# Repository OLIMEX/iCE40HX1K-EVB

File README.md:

# iCE40HX1K-EVB
FPGA development board made with KiCAD

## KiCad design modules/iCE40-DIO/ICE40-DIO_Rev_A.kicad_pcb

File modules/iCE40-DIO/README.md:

# Repository re-located here: https://github.com/OLIMEX/iCE40-DIO/tree/master

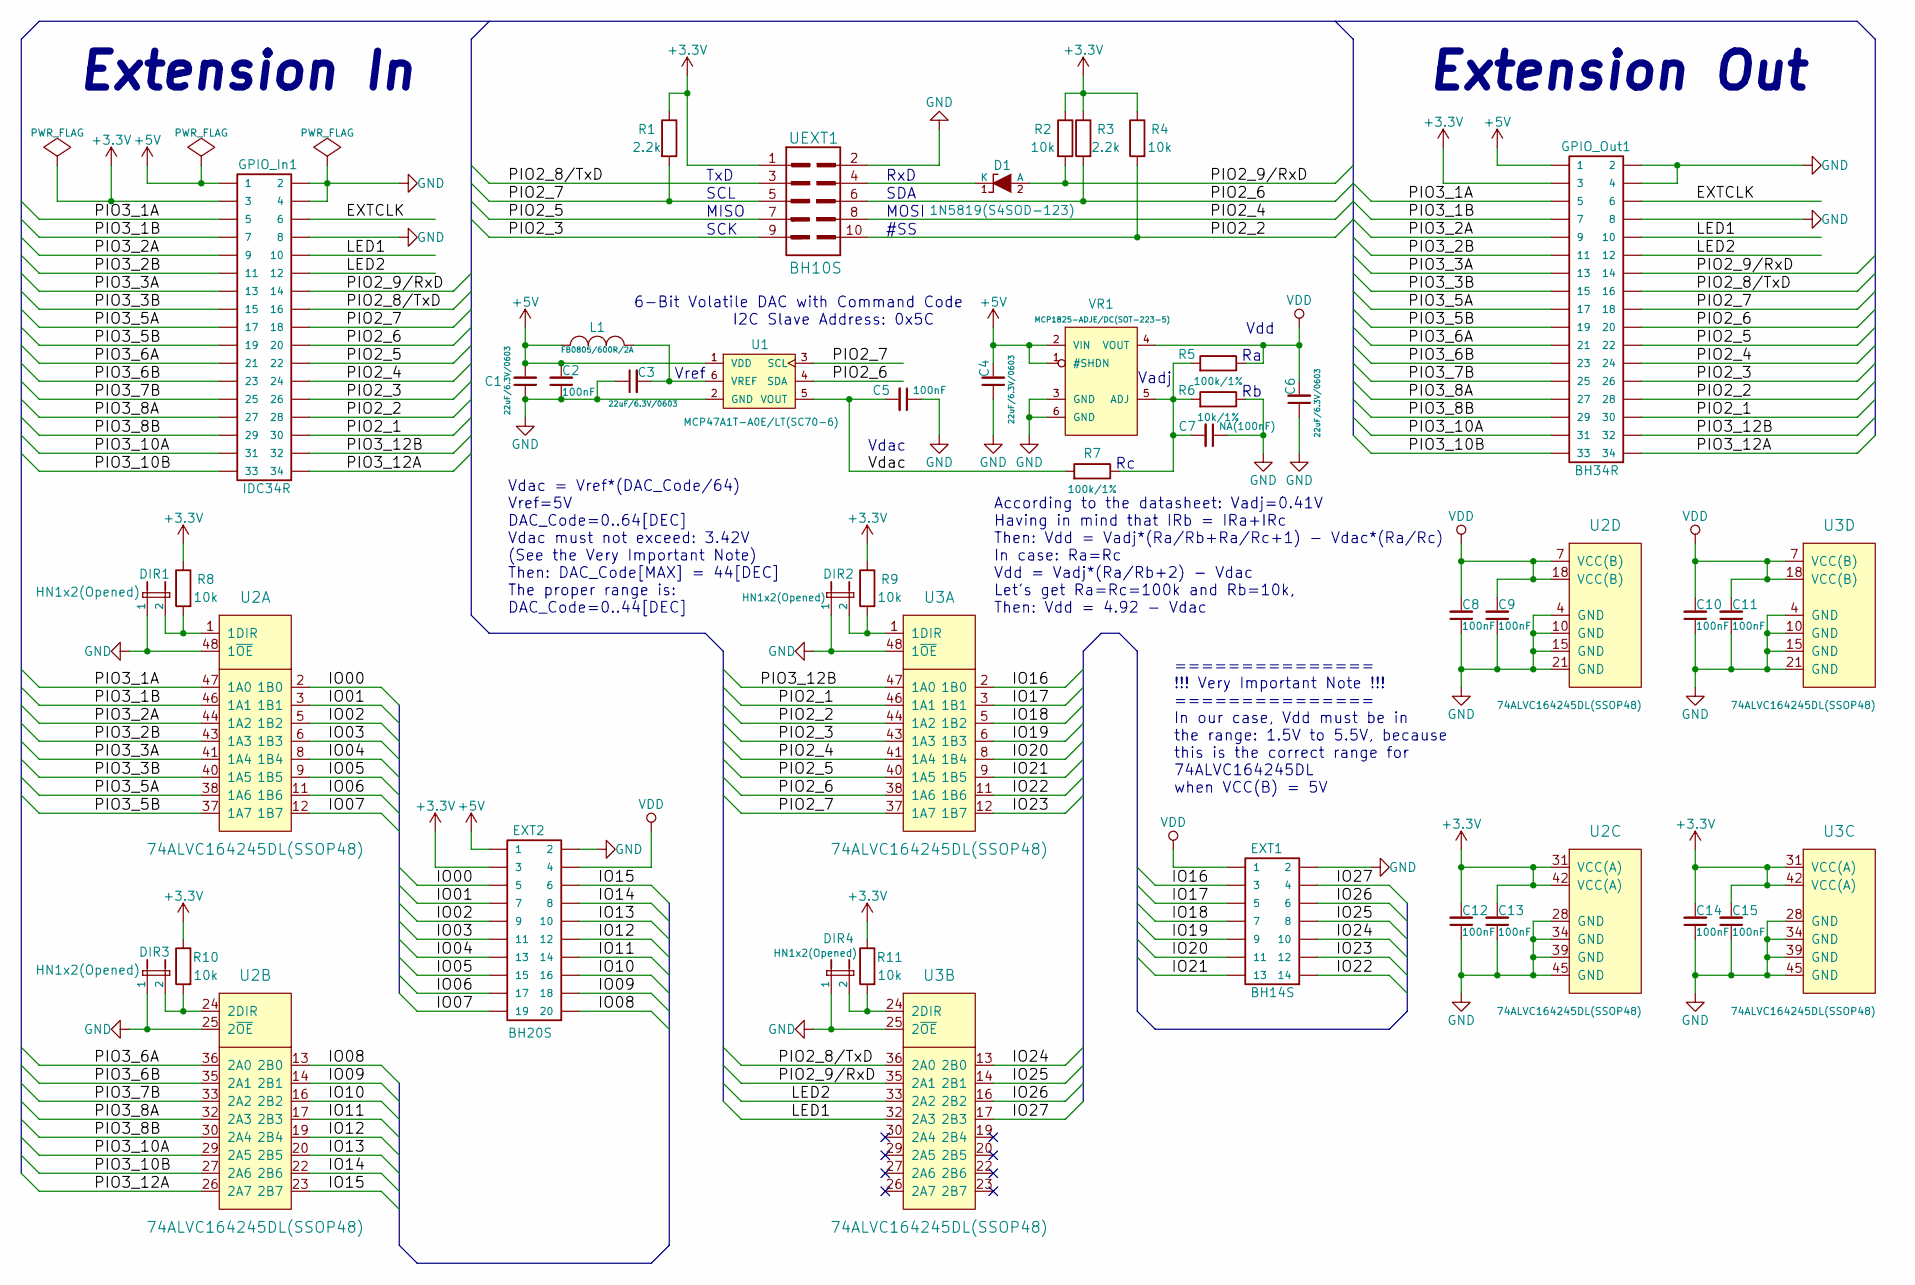
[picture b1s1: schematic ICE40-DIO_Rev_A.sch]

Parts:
C1, C3, C4, C6: 22uF/6.3V/0603; C_0603_5MIL_DWS
C2, C5, C8, C9, C10, C11, C12, C13, C14, C15: 100nF; C_0402_5MIL_DWS
C7: NA(100nF); C_0402_5MIL_DWS
D1: 1N5819(S4SOD-123); SOD-123_1C-2A_KA
DIR1, DIR2, DIR3, DIR4: HN1x2(Opened); HN1x2
EXT1: BH14S
EXT2: BH20S
GPIO_In1: IDC34R; IDC34R_PCB
GPIO_Out1: BH34R
L1: FB0805/600R/2A; L_0805_5MIL_DWS
R1, R3: 2.2k; R_0402_5MIL_DWS
R2, R4, R8, R9, R10, R11: 10k; R_0402_5MIL_DWS
R5, R7: 100k/1%; R_0402_5MIL_DWS
R6: 10k/1%; R_0402_5MIL_DWS
U1: MCP47A1T-A0E/LT(SC70-6); SC70-6_Pitch-0.65_2.00x2.10x1.00mm
U2, U3: 74ALVC164245DL(SSOP48); SSOP48_Pitch-0.635_16.00x10.40x2.80mm
UEXT1: BH10S
VR1: MCP1825-ADJE/DC(SOT-223-5); SOT-223-5_Pitch-1.27_6.50x7.00x1.80

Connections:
+3V3: C12.2, C13.2, C14.2, C15.2, EXT2.3, GPIO_In1.3, GPIO_Out1.3, R1.1, R2.1, R3.1, R4.1, R8.1, R9.1, R10.1, R11.1, U2.31 (VCC(A)), U2.42 (VCC(A)), U3.31 (VCC(A)), U3.42 (VCC(A)), UEXT1.1
+5V: C1.2, C2.2, C4.2, EXT2.1, GPIO_In1.1, GPIO_Out1.1, L1.2, U1.1 (VDD), VR1.1 (#SHDN), VR1.2 (VIN)
/EXTCLK: GPIO_In1.6, GPIO_Out1.6
/IO00: EXT2.5, U2.2 (1B0)
/IO01: EXT2.7, U2.3 (1B1)
/IO02: EXT2.9, U2.5 (1B2)
/IO03: EXT2.11, U2.6 (1B3)
/IO04: EXT2.13, U2.8 (1B4)
/IO05: EXT2.15, U2.9 (1B5)
/IO06: EXT2.17, U2.11 (1B6)
/IO07: EXT2.19, U2.12 (1B7)
/IO08: EXT2.20, U2.13 (2B0)
/IO09: EXT2.18, U2.14 (2B1)
/IO10: EXT2.16, U2.16 (2B2)
/IO11: EXT2.14, U2.17 (2B3)
/IO12: EXT2.12, U2.19 (2B4)
/IO13: EXT2.10, U2.20 (2B5)
/IO14: EXT2.8, U2.22 (2B6)
/IO15: EXT2.6, U2.23 (2B7)
/IO16: EXT1.3, U3.2 (1B0)
/IO17: EXT1.5, U3.3 (1B1)
/IO18: EXT1.7, U3.5 (1B2)
/IO19: EXT1.9, U3.6 (1B3)
/IO20: EXT1.11, U3.8 (1B4)
/IO21: EXT1.13, U3.9 (1B5)
/IO22: EXT1.14, U3.11 (1B6)
/IO23: EXT1.12, U3.12 (1B7)
/IO24: EXT1.10, U3.13 (2B0)
/IO25: EXT1.8, U3.14 (2B1)
/IO26: EXT1.6, U3.16 (2B2)
/IO27: EXT1.4, U3.17 (2B3)
/LED1: GPIO_In1.10, GPIO_Out1.10, U3.32 (2A3)
/LED2: GPIO_In1.12, GPIO_Out1.12, U3.33 (2A2)
/PIO2_1: GPIO_In1.30, GPIO_Out1.30, U3.46 (1A1)
/PIO2_2: GPIO_In1.28, GPIO_Out1.28, R4.2, U3.44 (1A2), UEXT1.10
/PIO2_3: GPIO_In1.26, GPIO_Out1.26, U3.43 (1A3), UEXT1.9
/PIO2_4: GPIO_In1.24, GPIO_Out1.24, U3.41 (1A4), UEXT1.8
/PIO2_5: GPIO_In1.22, GPIO_Out1.22, U3.40 (1A5), UEXT1.7
/PIO2_6: GPIO_In1.20, GPIO_Out1.20, R3.2, U1.4 (SDA), U3.38 (1A6), UEXT1.6
/PIO2_7: GPIO_In1.18, GPIO_Out1.18, R1.2, U1.3 (SCL), U3.37 (1A7), UEXT1.5
/PIO2_8/TxD: GPIO_In1.16, GPIO_Out1.16, U3.36 (2A0), UEXT1.3
/PIO2_9/RxD: D1.2 (A), GPIO_In1.14, GPIO_Out1.14, R2.2, U3.35 (2A1)
/PIO3_1A: GPIO_In1.5, GPIO_Out1.5, U2.47 (1A0)
/PIO3_1B: GPIO_In1.7, GPIO_Out1.7, U2.46 (1A1)
/PIO3_2A: GPIO_In1.9, GPIO_Out1.9, U2.44 (1A2)
/PIO3_2B: GPIO_In1.11, GPIO_Out1.11, U2.43 (1A3)
/PIO3_3A: GPIO_In1.13, GPIO_Out1.13, U2.41 (1A4)
/PIO3_3B: GPIO_In1.15, GPIO_Out1.15, U2.40 (1A5)
/PIO3_5A: GPIO_In1.17, GPIO_Out1.17, U2.38 (1A6)
/PIO3_5B: GPIO_In1.19, GPIO_Out1.19, U2.37 (1A7)
/PIO3_6A: GPIO_In1.21, GPIO_Out1.21, U2.36 (2A0)
/PIO3_6B: GPIO_In1.23, GPIO_Out1.23, U2.35 (2A1)
/PIO3_7B: GPIO_In1.25, GPIO_Out1.25, U2.33 (2A2)
/PIO3_8A: GPIO_In1.27, GPIO_Out1.27, U2.32 (2A3)
/PIO3_8B: GPIO_In1.29, GPIO_Out1.29, U2.30 (2A4)
/PIO3_10A: GPIO_In1.31, GPIO_Out1.31, U2.29 (2A5)
/PIO3_10B: GPIO_In1.33, GPIO_Out1.33, U2.27 (2A6)
/PIO3_12A: GPIO_In1.34, GPIO_Out1.34, U2.26 (2A7)
/PIO3_12B: GPIO_In1.32, GPIO_Out1.32, U3.47 (1A0)
/Vdac: C5.2, R7.2, U1.5 (VOUT)
GND: C1.1, C2.1, C3.1, C4.1, C5.1, C6.1, C7.1, C8.1, C9.1, C10.1, C11.1, C12.1, C13.1, C14.1, C15.1, DIR1.1, DIR2.1, DIR3.1, DIR4.1, EXT1.2, EXT2.2, GPIO_In1.2, GPIO_In1.4, GPIO_In1.8, GPIO_Out1.2, GPIO_Out1.4, GPIO_Out1.8, R6.1, U1.2 (GND), U2.4 (GND), U2.10 (GND), U2.15 (GND), U2.21 (GND), U2.25 (2~OE), U2.28 (GND), U2.34 (GND), U2.39 (GND), U2.45 (GND), U2.48 (1~OE), U3.4 (GND), U3.10 (GND), U3.15 (GND), U3.21 (GND), U3.25 (2~OE), U3.28 (GND), U3.34 (GND), U3.39 (GND), U3.45 (GND), U3.48 (1~OE), UEXT1.2, VR1.3 (GND), VR1.6 (GND)
unnamed: C3.2, L1.1, U1.6 (VREF)
unnamed: C7.2, R5.2, R6.2, R7.1, VR1.5 (ADJ)
unnamed: D1.1 (K), UEXT1.4
unnamed: DIR1.2, R8.2, U2.1 (1DIR)
unnamed: DIR2.2, R9.2, U3.1 (1DIR)
unnamed: DIR3.2, R10.2, U2.24 (2DIR)
unnamed: DIR4.2, R11.2, U3.24 (2DIR)
VDD: C6.2, C8.2, C9.2, C10.2, C11.2, EXT1.1, EXT2.4, R5.1, U2.7 (VCC(B)), U2.18 (VCC(B)), U3.7 (VCC(B)), U3.18 (VCC(B)), VR1.4 (VOUT)

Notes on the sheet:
Extension Out
Extension In
TxD
SCL
RxD
SDA
MISO
MOSI
SCK
#SS
According to the datasheet: Vadj=0.41V Having in mind that IRb = IRa+IRc Then: Vdd = Vadj*(Ra/Rb+Ra/Rc+1) - Vdac*(Ra/Rc) In case: Ra=Rc Vdd = Vadj*(Ra/Rb+2) - Vdac Let's get Ra=Rc=100k and Rb=10k, Then: Vdd = 4.92 - Vdac
Vdd
Vadj
Vdac
Vdac = Vref*(DAC_Code/64) Vref=5V DAC_Code=0..64[DEC] Vdac must not exceed: 3.42V (See the Very Important Note) Then: DAC_Code[MAX] = 44[DEC] The proper range is: DAC_Code=0..44[DEC]
Vref
=============== !!! Very Important Note !!! =============== In our case, Vdd must be in the range: 1.5V to 5.5V, because this is the correct range for 74ALVC164245DL when VCC(B) = 5V
6-Bit Volatile DAC with Command Code I2C Slave Address: 0x5C

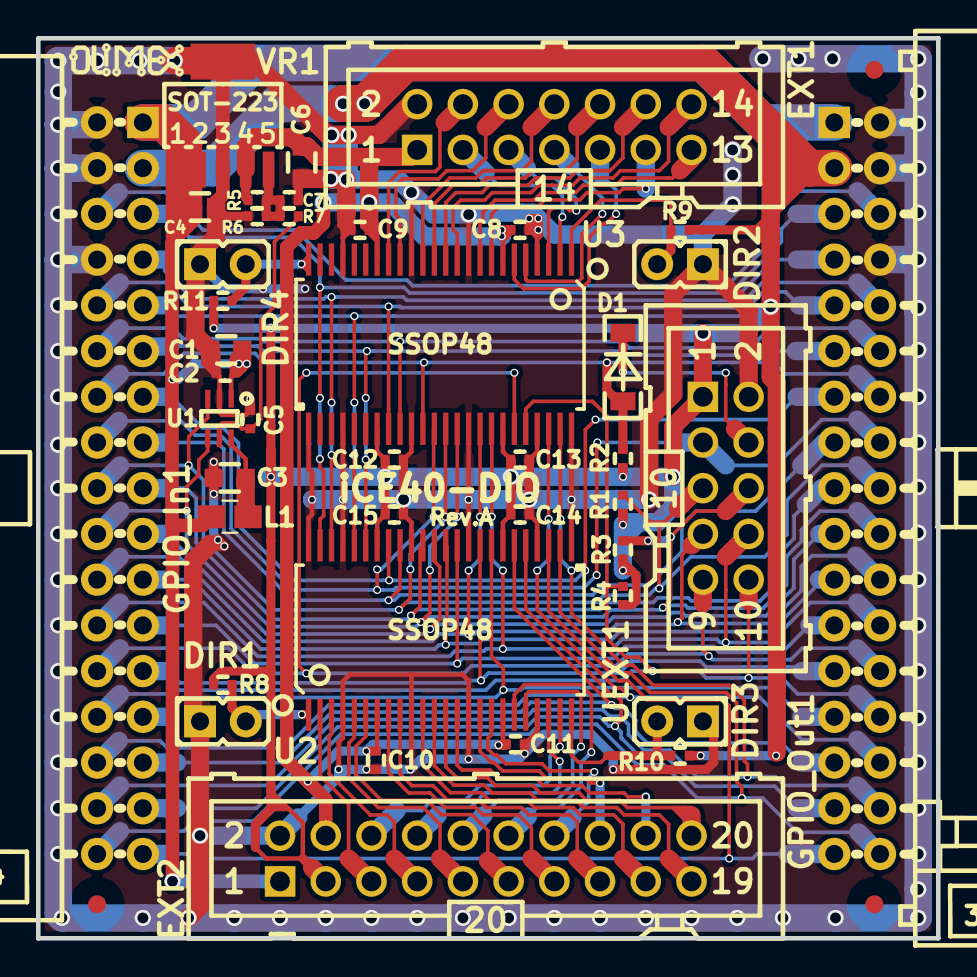
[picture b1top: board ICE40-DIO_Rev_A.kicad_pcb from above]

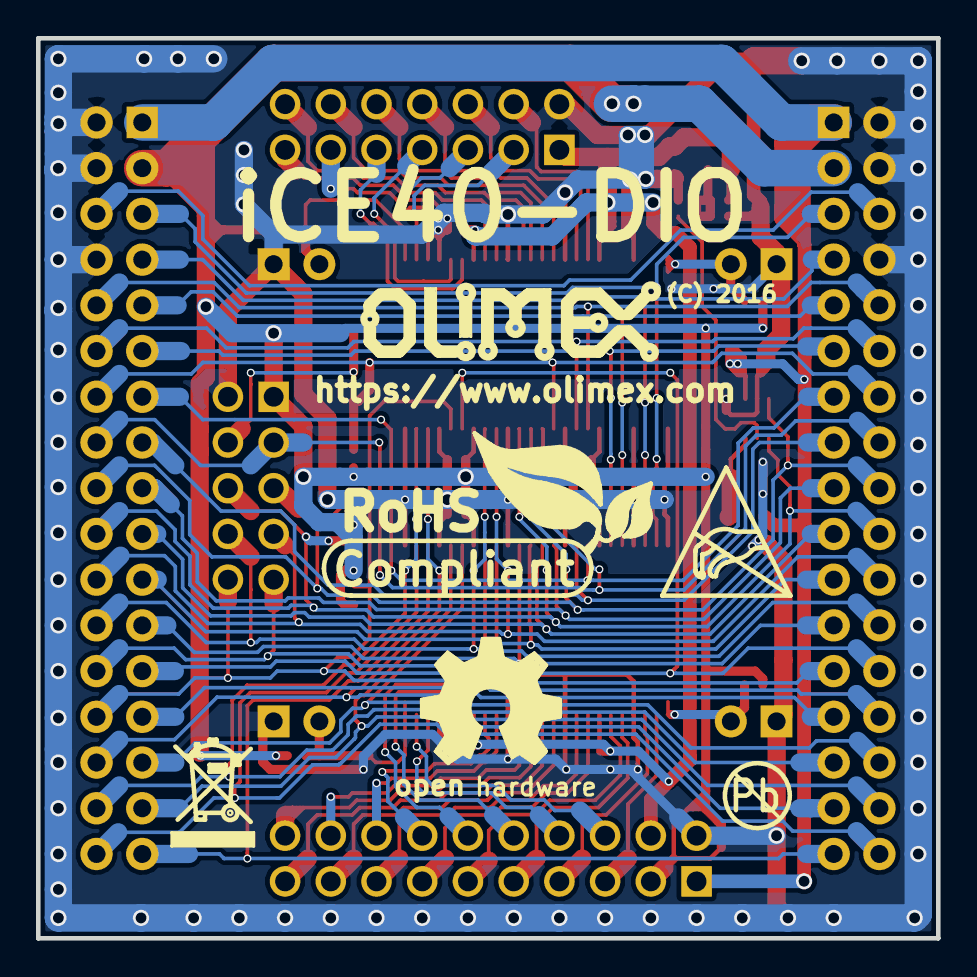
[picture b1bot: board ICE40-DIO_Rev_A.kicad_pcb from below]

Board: 2 copper layers, 50.0 x 50.0 mm, 43 parts (2 on the bottom side), 69 nets.

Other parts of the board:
Ref**: Val**; LOGO_ANTISTATIC_1
Ref**#2: Val**; LOGO_ROHS_1

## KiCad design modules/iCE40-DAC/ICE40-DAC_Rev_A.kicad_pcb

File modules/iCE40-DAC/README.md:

# Repository re-located here: https://github.com/OLIMEX/iCE40-DAC/tree/master

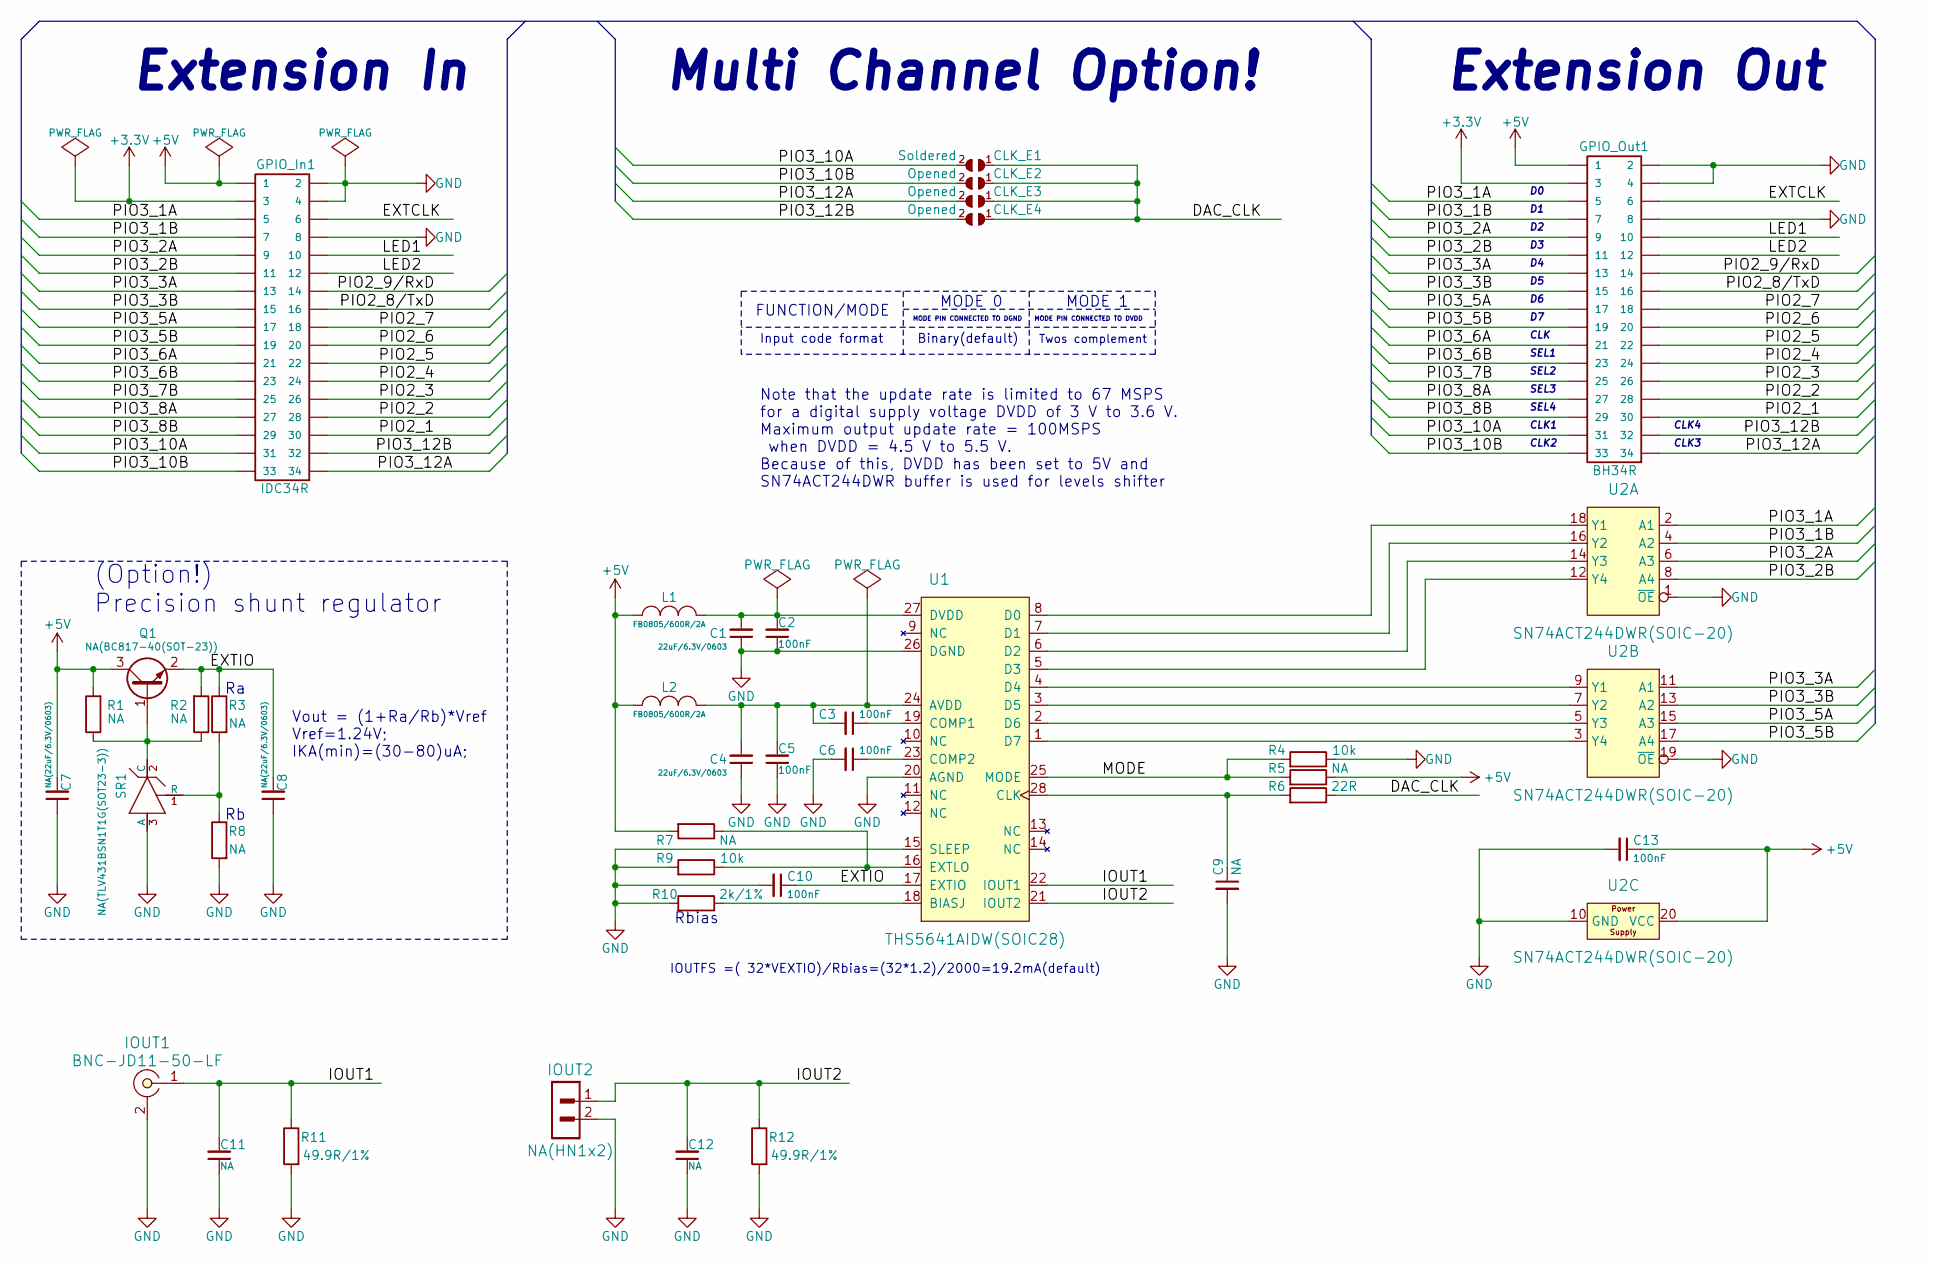
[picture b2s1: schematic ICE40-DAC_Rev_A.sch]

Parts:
C1, C4: 22uF/6.3V/0603; C_0603_5MIL_DWS
C2, C3, C5, C6, C10, C13: 100nF; C_0402_5MIL_DWS
C7, C8: NA(22uF/6.3V/0603); C_0603_5MIL_DWS
C9, C11, C12: NA; C_0402_5MIL_DWS
CLK_E1: Soldered; SJ
CLK_E2, CLK_E3, CLK_E4: Opened; SJ
GPIO_In1: IDC34R; IDC34R_PCB
GPIO_Out1: BH34R
IOUT1: BNC-JD11-50-LF; BNC-JD11-50-LF_1-IN_2-GND
IOUT2: NA(HN1x2); HN1x2
L1, L2: FB0805/600R/2A; L_0805_5MIL_DWS
Q1: NA(BC817-40(SOT-23)); SOT23
R1, R2, R3, R5, R7, R8: NA; R_0402_5MIL_DWS
R4, R9: 10k; R_0402_5MIL_DWS
R6: 22R; R_0402_5MIL_DWS
R10: 2k/1%; R_0402_5MIL_DWS
R11, R12: 49.9R/1%; R_0603_5MIL_DWS
SR1: NA(TLV431BSN1T1G(SOT23-3)); SOT-23
U1: THS5641AIDW(SOIC28); SOIC28-300
U2: SN74ACT244DWR(SOIC-20); SOIC20_300mil

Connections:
+3V3: GPIO_In1.3, GPIO_Out1.3
+5V: C7.2, C13.1, GPIO_In1.1, GPIO_Out1.1, L1.2, L2.1, Q1.3 (C), R1.2, R5.1, R7.2, U2.20 (VCC)
/DAC_CLK: CLK_E1.1, CLK_E2.1, CLK_E3.1, CLK_E4.1, R6.1
/EXTCLK: GPIO_In1.6, GPIO_Out1.6
/EXTIO: C8.2, C10.1, Q1.2 (E), R2.2, R3.1, U1.17 (EXTIO)
/IOUT1: C11.2, IOUT1.1, R11.1, U1.22 (IOUT1)
/IOUT2: C12.2, IOUT2.1, R12.1, U1.21 (IOUT2)
/LED1: GPIO_In1.10, GPIO_Out1.10
/LED2: GPIO_In1.12, GPIO_Out1.12
/MODE: R4.2, R5.2, U1.25 (MODE)
/PIO2_1: GPIO_In1.30, GPIO_Out1.30
/PIO2_2: GPIO_In1.28, GPIO_Out1.28
/PIO2_3: GPIO_In1.26, GPIO_Out1.26
/PIO2_4: GPIO_In1.24, GPIO_Out1.24
/PIO2_5: GPIO_In1.22, GPIO_Out1.22
/PIO2_6: GPIO_In1.20, GPIO_Out1.20
/PIO2_7: GPIO_In1.18, GPIO_Out1.18
/PIO2_8/TxD: GPIO_In1.16, GPIO_Out1.16
/PIO2_9/RxD: GPIO_In1.14, GPIO_Out1.14
/PIO3_1A: GPIO_In1.5, GPIO_Out1.5, U2.2 (A1)
/PIO3_1B: GPIO_In1.7, GPIO_Out1.7, U2.4 (A2)
/PIO3_2A: GPIO_In1.9, GPIO_Out1.9, U2.6 (A3)
/PIO3_2B: GPIO_In1.11, GPIO_Out1.11, U2.8 (A4)
/PIO3_3A: GPIO_In1.13, GPIO_Out1.13, U2.11 (A1)
/PIO3_3B: GPIO_In1.15, GPIO_Out1.15, U2.13 (A2)
/PIO3_5A: GPIO_In1.17, GPIO_Out1.17, U2.15 (A3)
/PIO3_5B: GPIO_In1.19, GPIO_Out1.19, U2.17 (A4)
/PIO3_6A: GPIO_In1.21, GPIO_Out1.21
/PIO3_6B: GPIO_In1.23, GPIO_Out1.23
/PIO3_7B: GPIO_In1.25, GPIO_Out1.25
/PIO3_8A: GPIO_In1.27, GPIO_Out1.27
/PIO3_8B: GPIO_In1.29, GPIO_Out1.29
/PIO3_10A: CLK_E1.2, GPIO_In1.31, GPIO_Out1.31
/PIO3_10B: CLK_E2.2, GPIO_In1.33, GPIO_Out1.33
/PIO3_12A: CLK_E3.2, GPIO_In1.34, GPIO_Out1.34
/PIO3_12B: CLK_E4.2, GPIO_In1.32, GPIO_Out1.32
GND: C1.1, C2.1, C4.1, C5.1, C6.2, C7.1, C8.1, C9.2, C10.2, C11.1, C12.1, C13.2, GPIO_In1.2, GPIO_In1.4, GPIO_In1.8, GPIO_Out1.2, GPIO_Out1.4, GPIO_Out1.8, IOUT1.2, IOUT2.2, R4.1, R8.2, R9.2, R10.2, R11.2, R12.2, SR1.3 (A), U1.15 (SLEEP), U1.20 (AGND), U1.26 (DGND), U2.1 (~OE), U2.10 (GND), U2.19 (~OE)
unnamed: C1.2, C2.2, L1.1, U1.27 (DVDD)
unnamed: C3.1, U1.19 (COMP1)
unnamed: C3.2, C4.2, C5.2, L2.2, U1.24 (AVDD)
unnamed: C6.1, U1.23 (COMP2)
unnamed: C9.1, R6.2, U1.28 (CLK)
unnamed: Q1.1 (B), R1.1, R2.1, SR1.2 (C)
unnamed: R3.2, R8.1, SR1.1 (R)
unnamed: R7.1, R9.1, U1.16 (EXTLO)
unnamed: R10.1, U1.18 (BIASJ)
unnamed: U1.1 (D7), U2.3 (Y4)
unnamed: U1.2 (D6), U2.5 (Y3)
unnamed: U1.3 (D5), U2.7 (Y2)
unnamed: U1.4 (D4), U2.9 (Y1)
unnamed: U1.5 (D3), U2.12 (Y4)
unnamed: U1.6 (D2), U2.14 (Y3)
unnamed: U1.7 (D1), U2.16 (Y2)
unnamed: U1.8 (D0), U2.18 (Y1)

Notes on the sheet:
Extension Out
Extension In
Vout = (1+Ra/Rb)*Vref Vref=1.24V; IKA(min)=(30-80)uA;
(Option!) Precision shunt regulator
Multi Channel Option!
CLK
SEL1
SEL2
SEL3
SEL4
Note that the update rate is limited to 67 MSPS for a digital supply voltage DVDD of 3 V to 3.6 V. Maximum output update rate = 100MSPS when DVDD = 4.5 V to 5.5 V. Because of this, DVDD has been set to 5V and SN74ACT244DWR buffer is used for levels shifter
Rbias
IOUTFS =( 32*VEXTIO)/Rbias=(32*1.2)/2000=19.2mA(default)
FUNCTION/MODE
MODE 0
MODE 1
MODE PIN CONNECTED TO DGND
MODE PIN CONNECTED TO DVDD
Input code format
Binary(default)
Twos complement
CLK1
CLK2
CLK3
CLK4

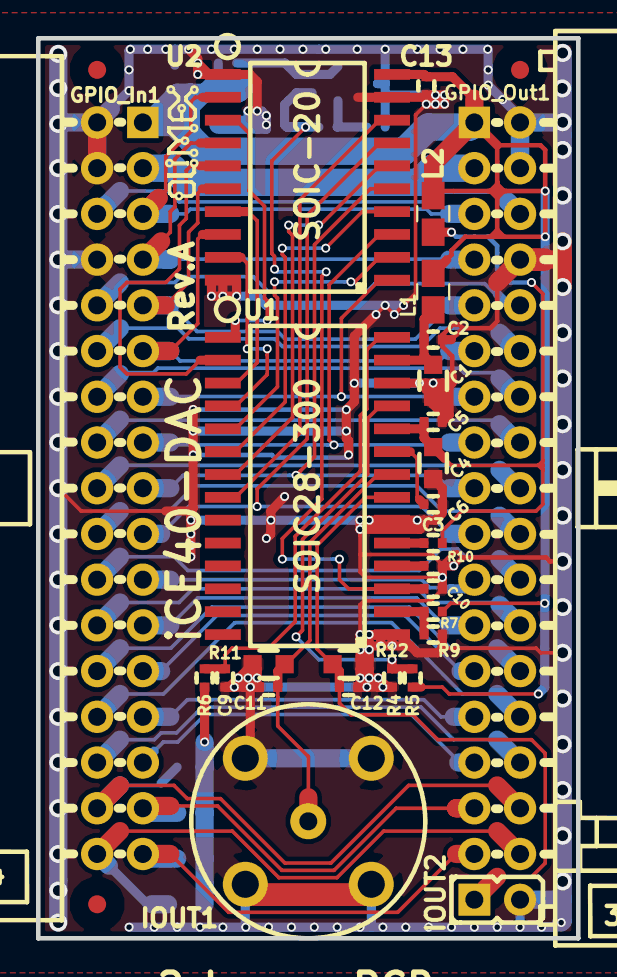
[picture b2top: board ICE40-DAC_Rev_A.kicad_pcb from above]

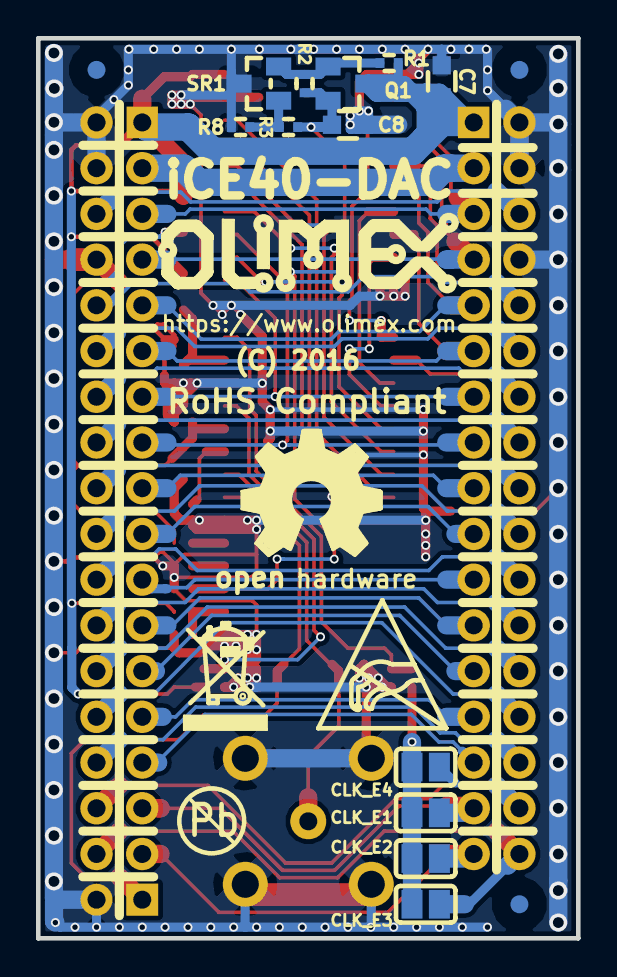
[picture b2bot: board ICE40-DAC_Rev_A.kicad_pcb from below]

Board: 2 copper layers, 30.0 x 50.0 mm, 40 parts (13 on the bottom side), 54 nets.

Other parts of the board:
Ref**: Val**; LOGO_ANTISTATIC_1

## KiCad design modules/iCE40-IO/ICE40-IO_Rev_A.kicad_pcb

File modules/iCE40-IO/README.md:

# Repository re-located here: https://github.com/OLIMEX/iCE40-IO/tree/master

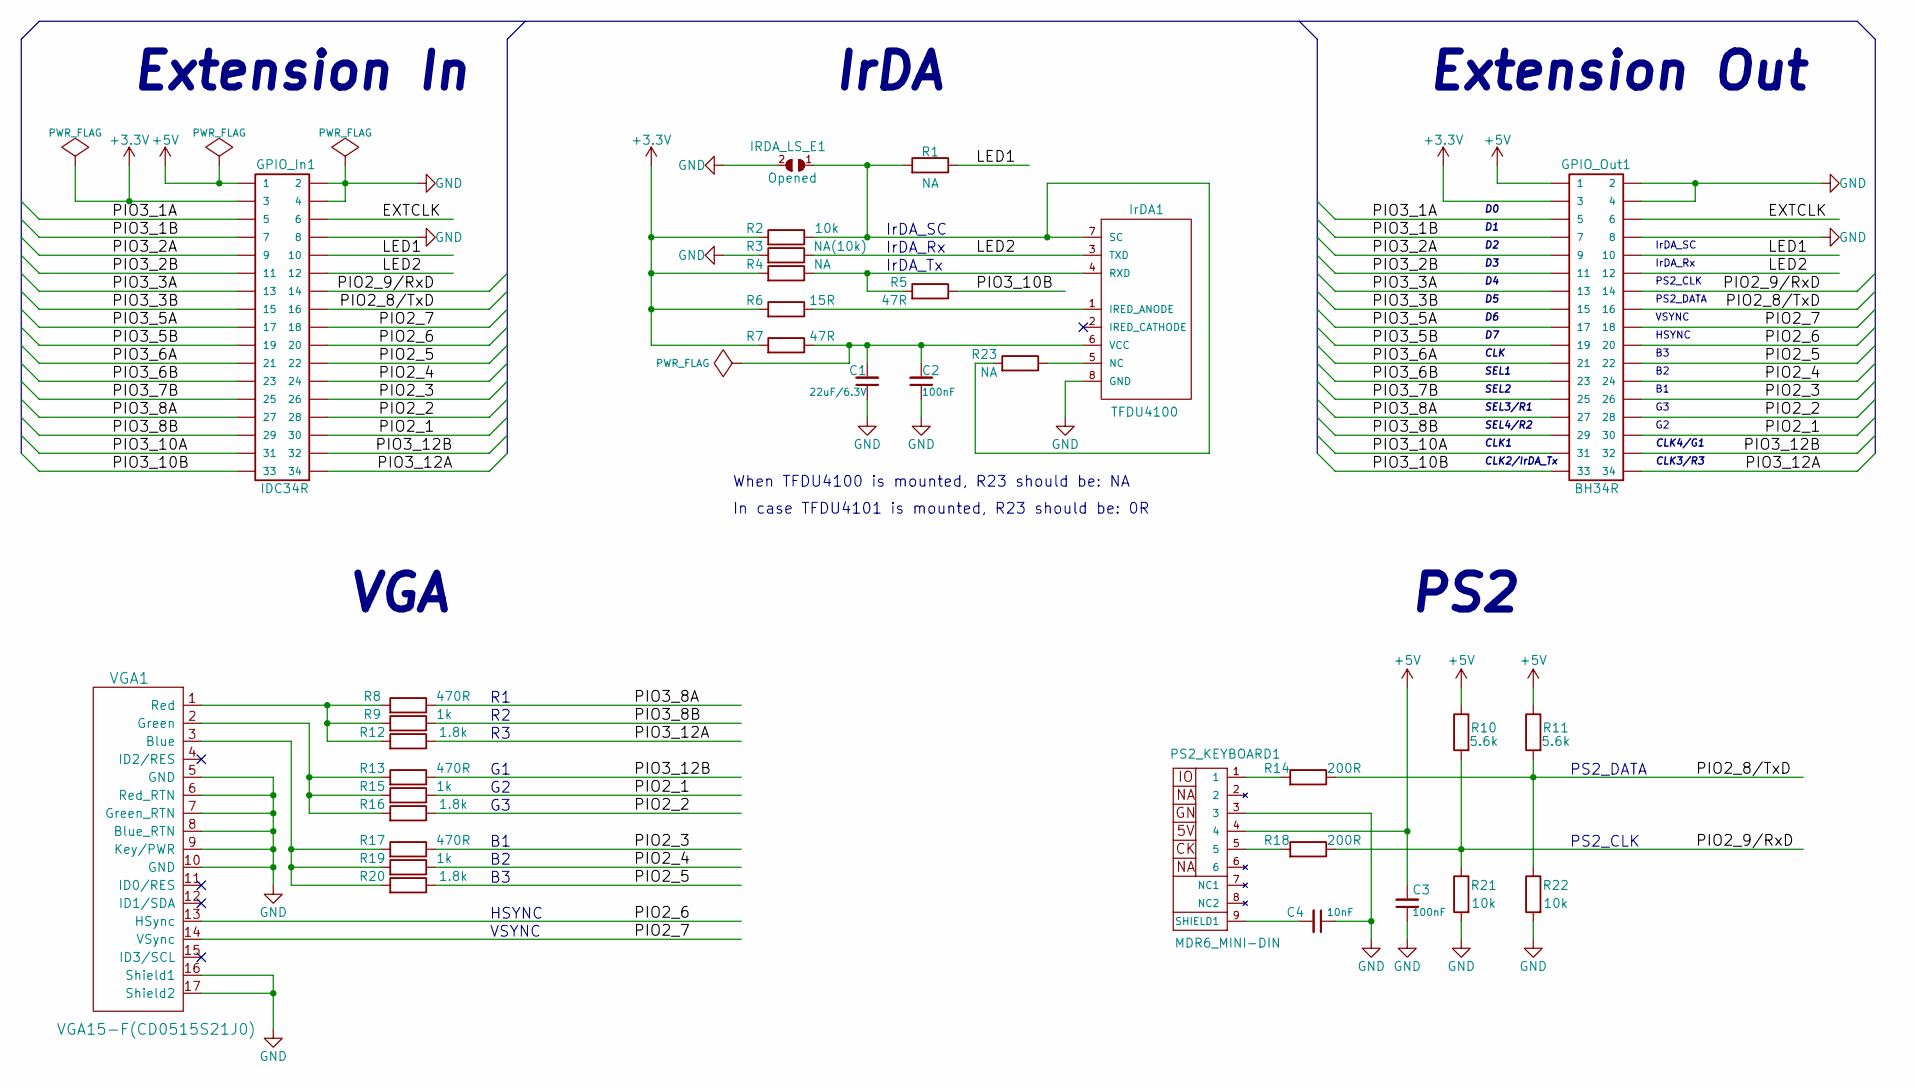
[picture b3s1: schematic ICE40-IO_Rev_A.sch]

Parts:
C1: 22uF/6.3V; C_0603_5MIL_DWS
C2, C3: 100nF; C_0402_5MIL_DWS
C4: 10nF; C_0402_5MIL_DWS
GPIO_In1: IDC34R; IDC34R_PCB
GPIO_Out1: BH34R
IRDA_LS_E1: Opened; SJ
IrDA1: TFDU4100; TFDU4100_PACK
PS2_KEYBOARD1: MDR6_MINI-DIN; PS2_MDR6_MINI-DIN
R1, R4, R23: NA; R_0402_5MIL_DWS
R2, R21, R22: 10k; R_0402_5MIL_DWS
R3: NA(10k); R_0402_5MIL_DWS
R5, R7: 47R; R_0805_5MIL_DWS
R6: 15R; R_1206_5MIL_DWS
R8, R13, R17: 470R; C_0603_5MIL_DWS
R9, R15, R19: 1k; C_0603_5MIL_DWS
R10, R11: 5.6k; R_0402_5MIL_DWS
R12, R16, R20: 1.8k; C_0603_5MIL_DWS
R14, R18: 200R; R_0402_5MIL_DWS
VGA1: VGA15-F(CD0515S21J0)

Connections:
+3V3: GPIO_In1.3, GPIO_Out1.3, R2.2, R4.2, R6.2, R7.2
+5V: C3.2, GPIO_In1.1, GPIO_Out1.1, PS2_KEYBOARD1.4, R10.1, R11.1
/EXTCLK: GPIO_In1.6, GPIO_Out1.6
/LED1: GPIO_In1.10, GPIO_Out1.10, R1.1
/LED2: GPIO_In1.12, GPIO_Out1.12, IrDA1.3 (TXD), R3.1
/PIO2_1: GPIO_In1.30, GPIO_Out1.30, R15.1
/PIO2_2: GPIO_In1.28, GPIO_Out1.28, R16.1
/PIO2_3: GPIO_In1.26, GPIO_Out1.26, R17.1
/PIO2_4: GPIO_In1.24, GPIO_Out1.24, R19.1
/PIO2_5: GPIO_In1.22, GPIO_Out1.22, R20.1
/PIO2_6: GPIO_In1.20, GPIO_Out1.20, VGA1.13 (HSync)
/PIO2_7: GPIO_In1.18, GPIO_Out1.18, VGA1.14 (VSync)
/PIO2_8/TxD: GPIO_In1.16, GPIO_Out1.16, R11.2, R14.1, R22.1
/PIO2_9/RxD: GPIO_In1.14, GPIO_Out1.14, R10.2, R18.1, R21.1
/PIO3_1A: GPIO_In1.5, GPIO_Out1.5
/PIO3_1B: GPIO_In1.7, GPIO_Out1.7
/PIO3_2A: GPIO_In1.9, GPIO_Out1.9
/PIO3_2B: GPIO_In1.11, GPIO_Out1.11
/PIO3_3A: GPIO_In1.13, GPIO_Out1.13
/PIO3_3B: GPIO_In1.15, GPIO_Out1.15
/PIO3_5A: GPIO_In1.17, GPIO_Out1.17
/PIO3_5B: GPIO_In1.19, GPIO_Out1.19
/PIO3_6A: GPIO_In1.21, GPIO_Out1.21
/PIO3_6B: GPIO_In1.23, GPIO_Out1.23
/PIO3_7B: GPIO_In1.25, GPIO_Out1.25
/PIO3_8A: GPIO_In1.27, GPIO_Out1.27, R8.1
/PIO3_8B: GPIO_In1.29, GPIO_Out1.29, R9.1
/PIO3_10A: GPIO_In1.31, GPIO_Out1.31
/PIO3_10B: GPIO_In1.33, GPIO_Out1.33, R5.1
/PIO3_12A: GPIO_In1.34, GPIO_Out1.34, R12.1
/PIO3_12B: GPIO_In1.32, GPIO_Out1.32, R13.1
GND: C1.1, C2.1, C3.1, C4.1, GPIO_In1.2, GPIO_In1.4, GPIO_In1.8, GPIO_Out1.2, GPIO_Out1.4, GPIO_Out1.8, IRDA_LS_E1.2, IrDA1.8 (GND), PS2_KEYBOARD1.3, R3.2, R21.2, R22.2, VGA1.5 (GND), VGA1.6 (Red_RTN), VGA1.7 (Green_RTN), VGA1.8 (Blue_RTN), VGA1.9 (Key/PWR), VGA1.10 (GND), VGA1.16 (Shield1), VGA1.17 (Shield2)
unnamed: C1.2, C2.2, IrDA1.6 (VCC), R7.1
unnamed: C4.2, PS2_KEYBOARD1.9 (SHIELD1)
unnamed: IRDA_LS_E1.1, IrDA1.7 (SC), R1.2, R2.1, R23.2
unnamed: IrDA1.1 (IRED_ANODE), R6.1
unnamed: IrDA1.4 (RXD), R4.1, R5.2
unnamed: IrDA1.5 (NC), R23.1
unnamed: PS2_KEYBOARD1.1, R14.2
unnamed: PS2_KEYBOARD1.5, R18.2
unnamed: R8.2, R9.2, R12.2, VGA1.1 (Red)
unnamed: R13.2, R15.2, R16.2, VGA1.2 (Green)
unnamed: R17.2, R19.2, R20.2, VGA1.3 (Blue)

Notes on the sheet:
Extension Out
Extension In
CLK
SEL1
SEL2
SEL3/R1
SEL4/R2
CLK1
CLK2/IrDA_Tx
CLK3/R3
CLK4/G1
HSYNC
VSYNC
PS2_CLK
PS2_DATA
IrDA_Rx
IrDA_Tx
IrDA_SC
IrDA
VGA
PS2
When TFDU4100 is mounted, R23 should be: NA
In case TFDU4101 is mounted, R23 should be: 0R

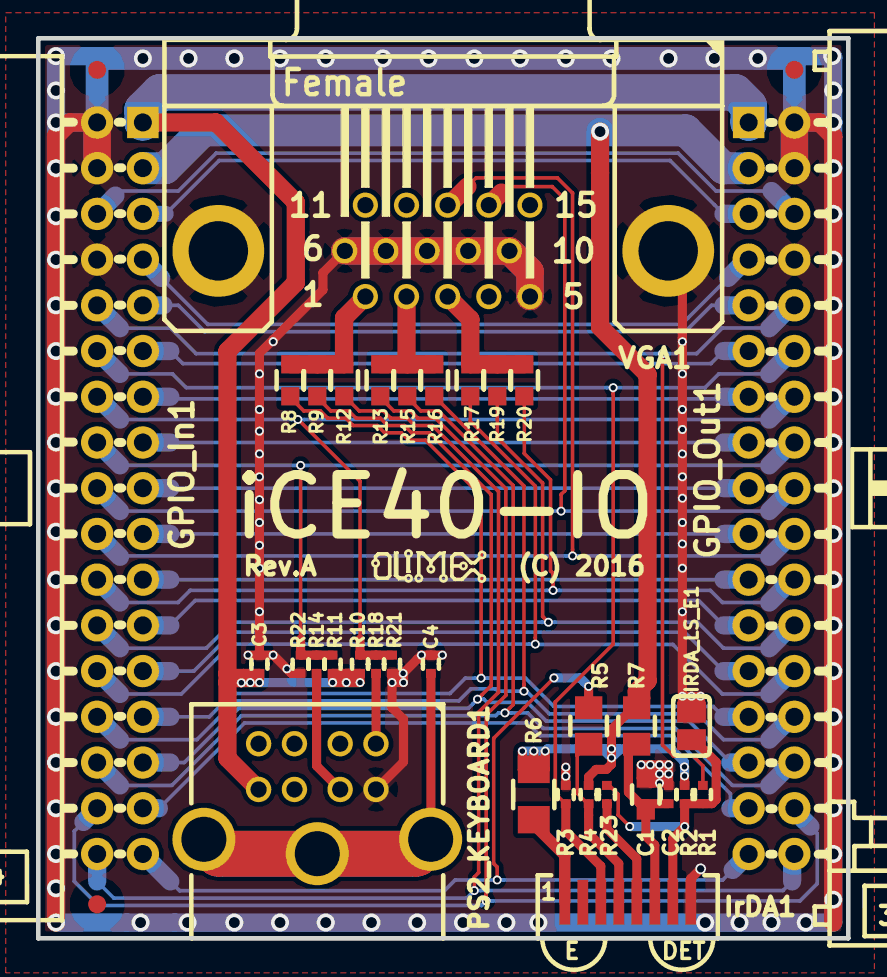
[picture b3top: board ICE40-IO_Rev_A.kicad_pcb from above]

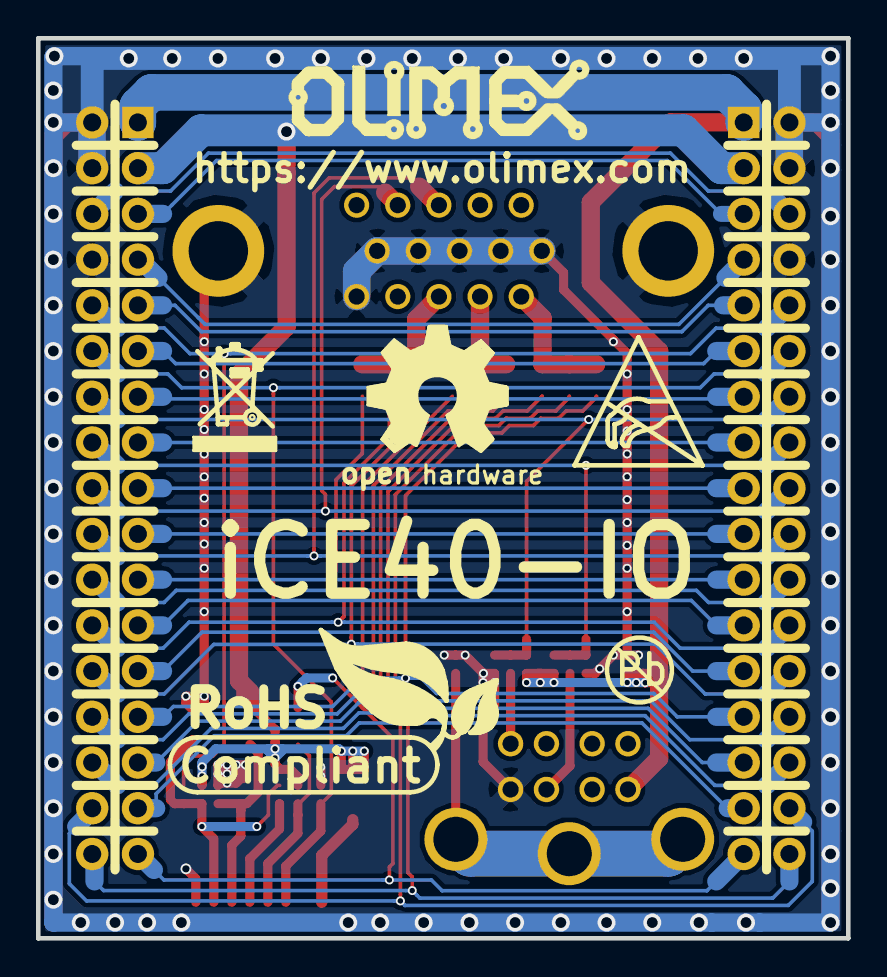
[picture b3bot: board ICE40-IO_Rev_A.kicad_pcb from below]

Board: 2 copper layers, 45.0 x 50.0 mm, 35 parts (2 on the bottom side), 43 nets.

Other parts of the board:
Ref**: Val**; LOGO_ROHS_1
Ref**#2: Val**; LOGO_ANTISTATIC_1

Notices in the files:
iCE40HX1K-EVB_Rev_B.kicad_pcb:
(C) 2016
